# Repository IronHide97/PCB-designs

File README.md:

# PCB-designs
```A public repository for pcb designers. This repositoriy will contain the schematics, PCB layouts, GERBER files and the 3D rendred images of PCB.```

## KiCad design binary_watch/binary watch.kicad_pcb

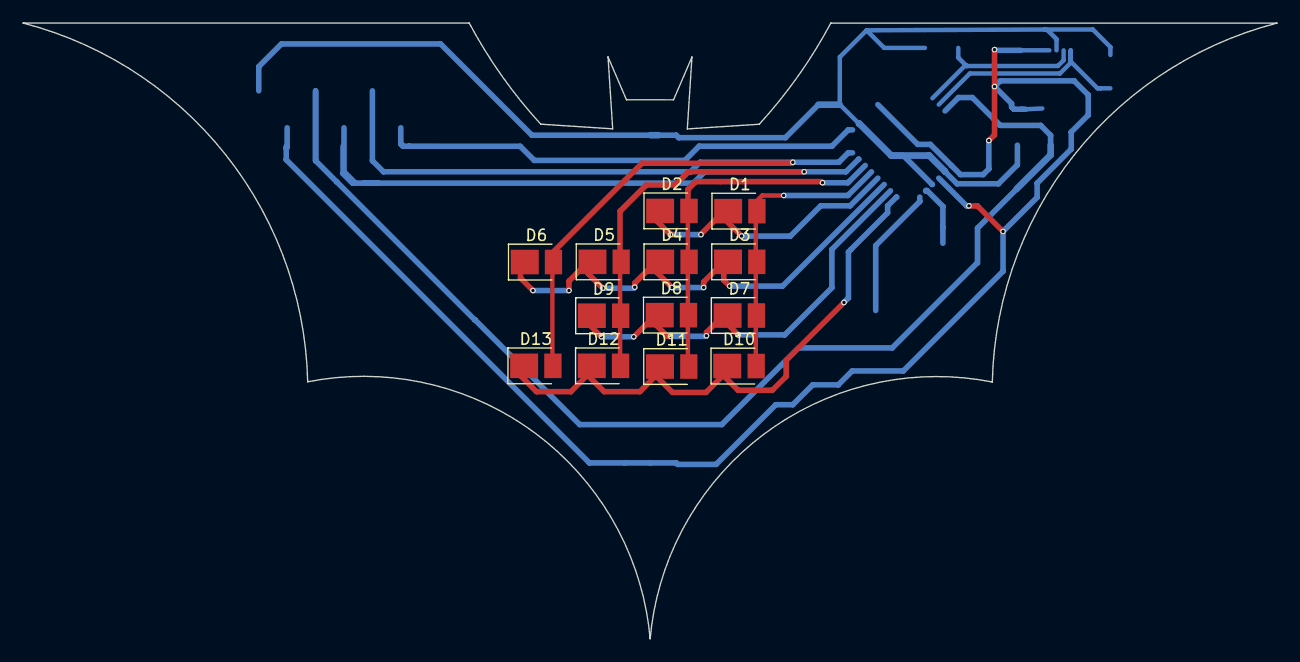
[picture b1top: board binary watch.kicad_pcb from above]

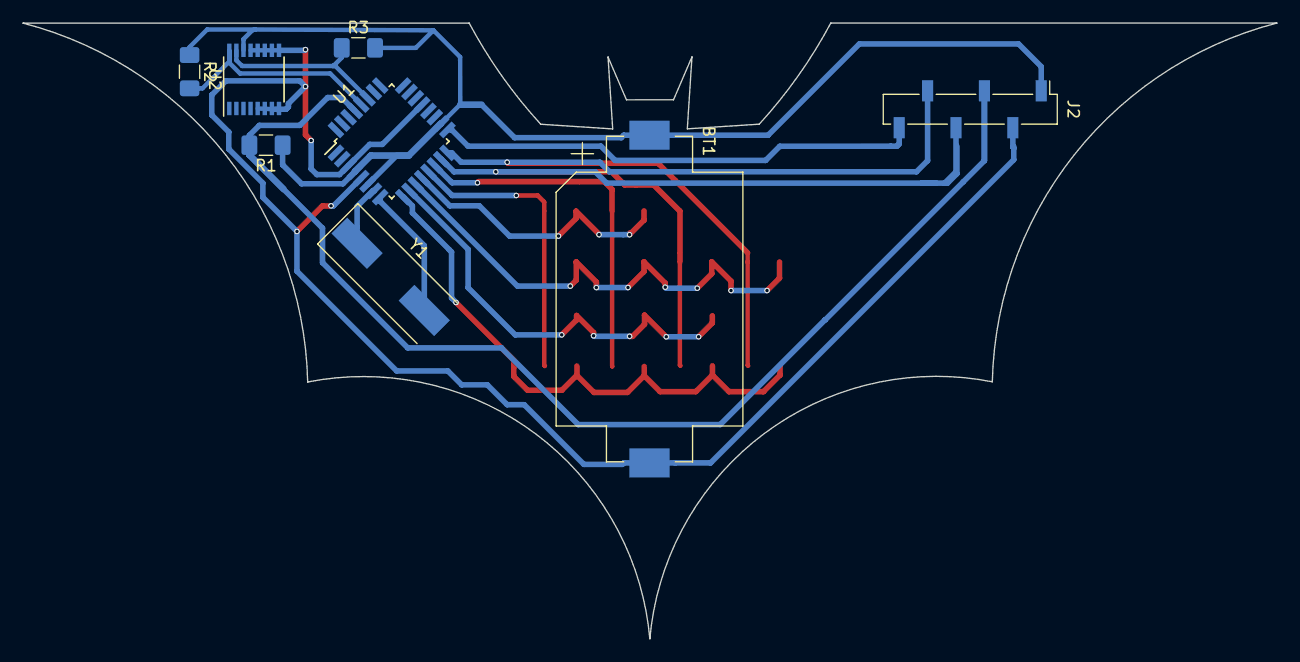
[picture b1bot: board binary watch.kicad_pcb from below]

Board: 2 copper layers, 112.1 x 55.1 mm, 21 parts (8 on the bottom side), 16 nets.

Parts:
BT1: Battery_Cell; BatteryHolder_Keystone_1060_1x2032
D1, D2, D3, D4, D5, D6, D7, D8, D9, D10, D11, D12, D13: LED; LED_PLCC_2835_Handsoldering
J2: Conn_01x06_Female; PinSocket_1x06_P2.54mm_Vertical_SMD_Pin1Left
R1, R2, R3: R; R_1206_3216Metric_Pad1.42x1.75mm_HandSolder
U1: ATmega328P-AU; TQFP-32_7x7mm_P0.8mm
U2: DS3231S; SSOP-16_3.9x4.9mm_P0.635mm
Y1: Crystal; Crystal_SMD_HC49-SD

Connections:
3.3V: BT1.1, J2.1, R1.1, R2.1, R3.2, U1.4, U1.6, U1.18, U2.14
GND: BT1.2, J2.2, U1.3, U1.5, U1.21, U2.5, U2.6, U2.7, U2.8, U2.9, U2.10, U2.11, U2.12, U2.13
MISO: D6.2, D13.2, J2.5, U1.16
MOSI: D5.2, D9.2, D12.2, J2.4, U1.15
unnamed: U1.7, Y1.1
unnamed: U1.8, Y1.2
RST: J2.3, R1.2, U1.29
SCK: J2.6, U1.17
SCL: R2.2, U1.28, U2.16
SDA: R3.1, U1.27, U2.15
b1: D1.2, D3.2, D7.2, D10.2, U1.13
b2: D2.2, D4.2, D8.2, D11.2, U1.14
h1: D1.1, D2.1, U1.12
h2: D3.1, D4.1, D5.1, D6.1, U1.11
m1: D7.1, D8.1, D9.1, U1.10
m2: D10.1, D11.1, D12.1, D13.1, U1.9

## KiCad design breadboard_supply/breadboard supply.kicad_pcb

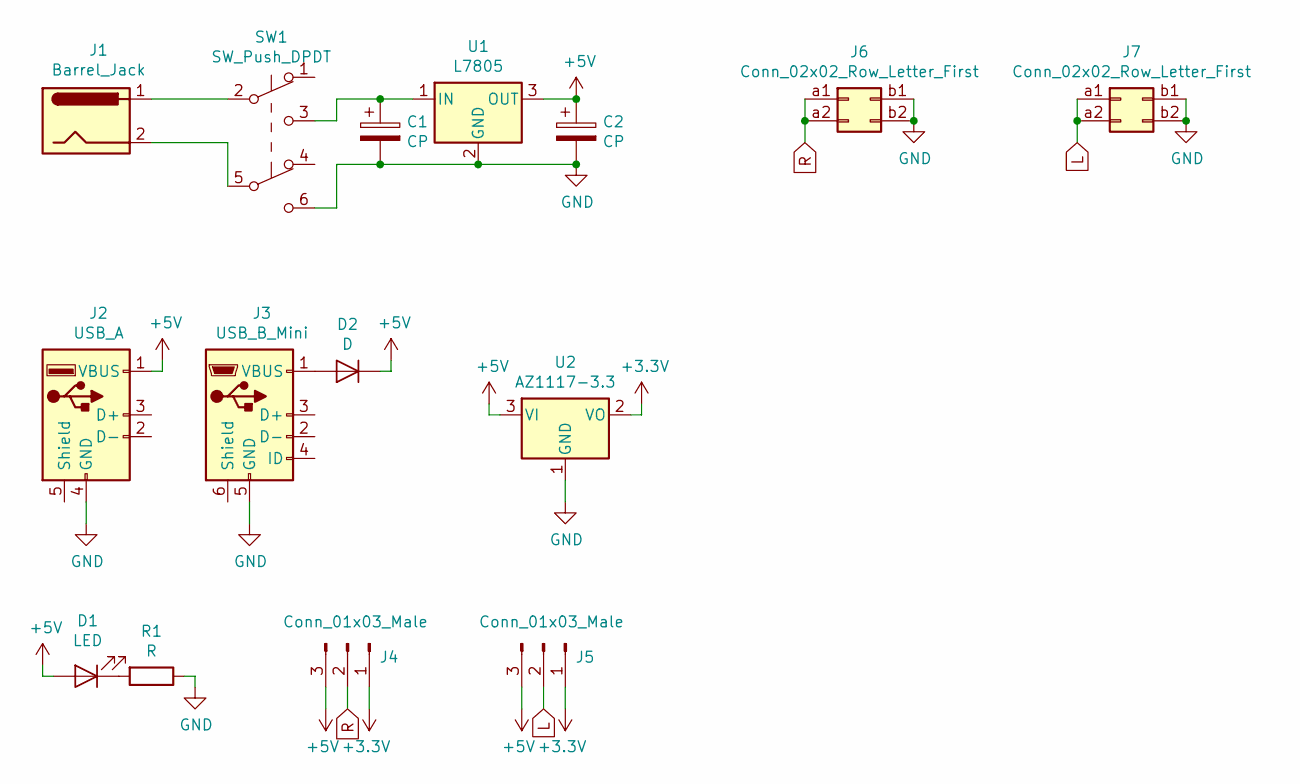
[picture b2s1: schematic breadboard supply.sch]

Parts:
C1, C2: CP; CP_Radial_D5.0mm_P2.50mm
D1: LED; LED_D3.0mm_FlatTop
D2: D; D_A-405_P7.62mm_Horizontal
J1: Barrel_Jack; BarrelJack_Horizontal
J2: USB_A; USB_A_Stewart_SS-52100-001_Horizontal
J3: USB_B_Mini; USB_Micro-B_Molex_47346-0001
J4, J5: Conn_01x03_Male; PinHeader_1x03_P2.54mm_Vertical
J6, J7: Conn_02x02_Row_Letter_First; PinHeader_2x02_P2.54mm_Vertical
R1: R; R_Axial_DIN0204_L3.6mm_D1.6mm_P7.62mm_Horizontal
SW1: SW_Push_DPDT; MPSA22E080150
U1: L7805; TO-220-3_Horizontal_TabDown
U2: AZ1117-3.3; SOT-223-3_TabPin2

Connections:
+3V3: J4.1, J5.1, U2.2 (VO)
+5V: C2.1, D1.2 (A), D2.1 (K), J2.1 (VBUS), J4.3, J5.3, U1.3 (OUT), U2.3 (VI)
GND: C1.2, C2.2, J2.4 (GND), J3.5 (GND), J6.b1, J6.b2, J7.b1, J7.b2, R1.1, SW1.6 (C), U1.2 (GND), U2.1 (GND)
L: J5.2, J7.a1, J7.a2
unnamed: C1.1, SW1.3 (C), U1.1 (IN)
unnamed: D1.1 (K), R1.2
unnamed: D2.2 (A), J3.1 (VBUS)
unnamed: J1.1, SW1.2 (B)
unnamed: J1.2, SW1.5 (B)
R: J4.2, J6.a1, J6.a2

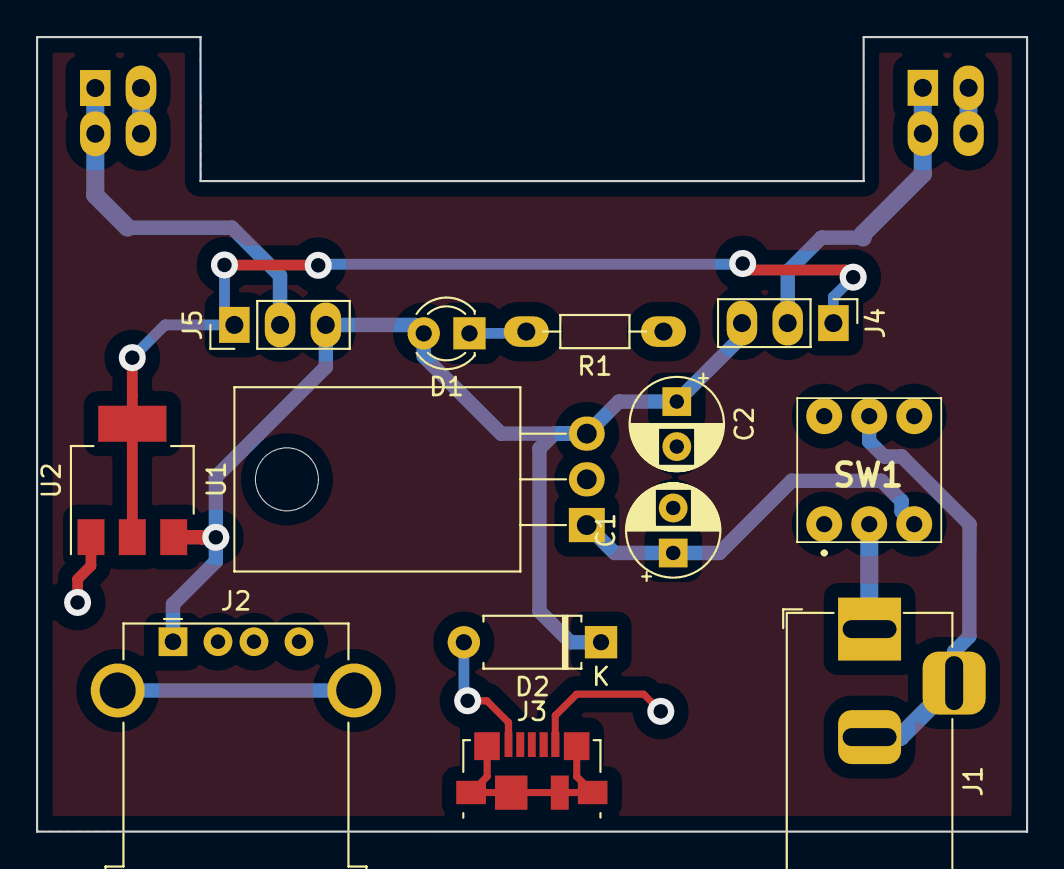
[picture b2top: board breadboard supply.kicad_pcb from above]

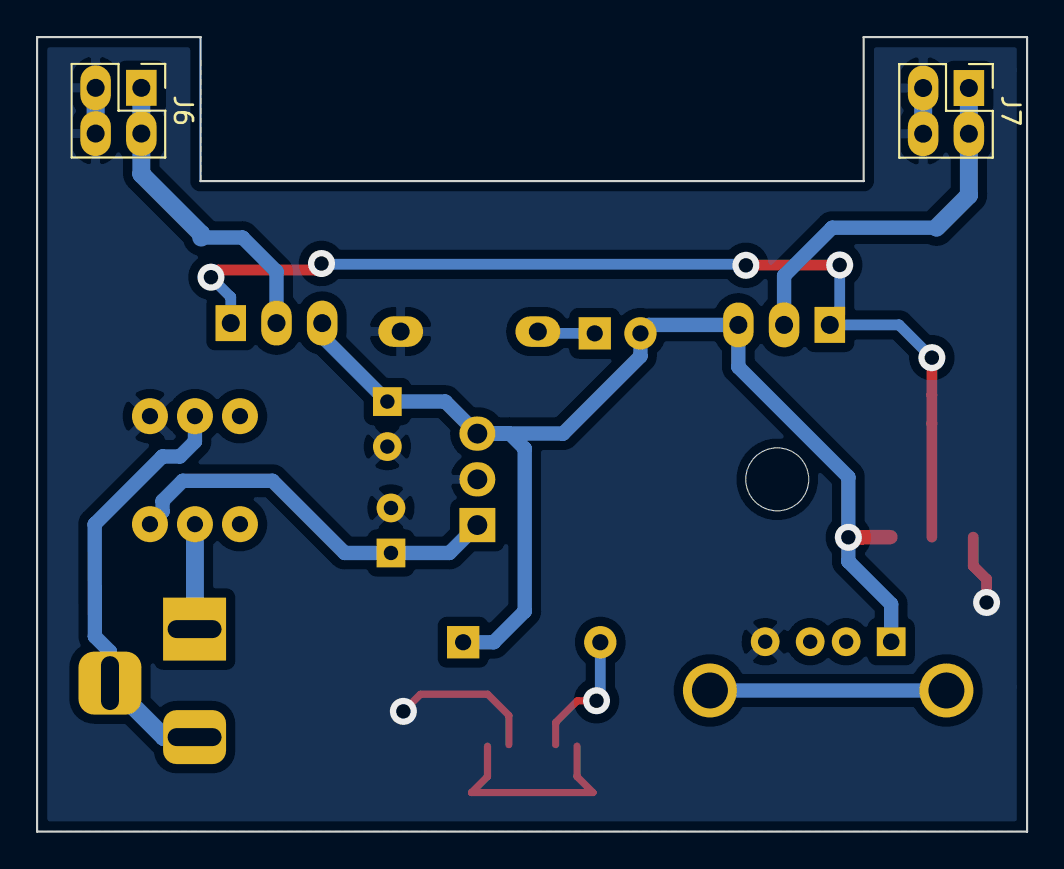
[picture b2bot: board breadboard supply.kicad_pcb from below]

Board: 2 copper layers, 55.0 x 44.1 mm, 15 parts (2 on the bottom side), 10 nets.

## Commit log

2021-06-19 breadborad power supply board
2021-06-19 binary watch batman logo
2021-06-22 demo txt
